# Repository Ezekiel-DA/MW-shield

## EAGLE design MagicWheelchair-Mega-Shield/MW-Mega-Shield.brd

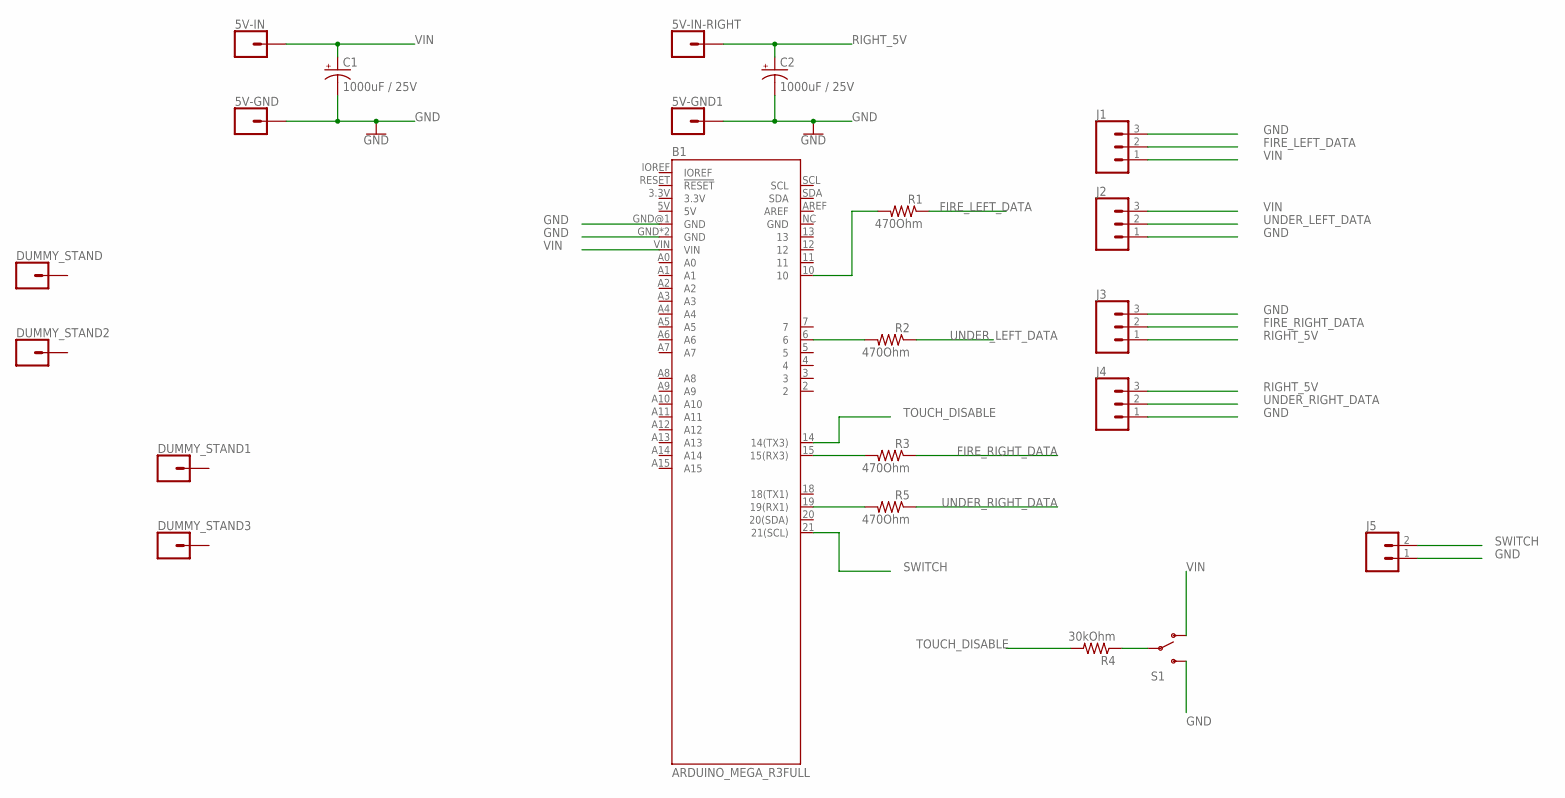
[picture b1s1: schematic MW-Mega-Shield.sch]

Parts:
5V-GND, 5V-GND1, 5V-IN, 5V-IN-RIGHT: CONN_01; 1X01
B1: ARDUINO_MEGA_R3FULL; ARDUINO_MEGA_NO_SILK
C1, C2: 1000uF / 25V; E5-10,5
DUMMY_STAND, DUMMY_STAND1, DUMMY_STAND2, DUMMY_STAND3: CONN_01; 1X01
J1, J2, J3, J4: CONN_03SCREW-NS; SCREWTERMINAL-3.5MM-3-NS
J5: CONN_02; 1X02
R1, R2, R3, R5: 470Ohm; R0603
R4: 30kOhm; R0603
S1: SWITCH-SPDTSMD; SWITCH_SPDT_SMD

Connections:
FIRE_LEFT_DATA: J1.2, R1.1
FIRE_RIGHT_DATA: J3.2, R3.1
GND: 5V-GND.1, 5V-GND1.1, B1.GND, B1.GND@1 (GND), B1.GND@4 (GND), C1.-, C2.-, J1.3, J2.1, J3.3, J4.1, J5.1, S1.3 (S)
unnamed: B1.10, R1.2
unnamed: B1.6, R2.2
unnamed: R4.1, S1.2
unnamed: B1.15 (15(RX3)), R3.2
unnamed: B1.19 (19(RX1)), R5.2
RIGHT_5V: 5V-IN-RIGHT.1, C2.+, J3.1, J4.3
SWITCH: B1.21 (21(SCL)), J5.2
TOUCH_DISABLE: B1.14 (14(TX3)), R4.2
UNDER_LEFT_DATA: J2.2, R2.1
UNDER_RIGHT_DATA: J4.2, R5.1
VIN: 5V-IN.1, B1.VIN, C1.+, J1.1, J2.3, S1.1 (O)

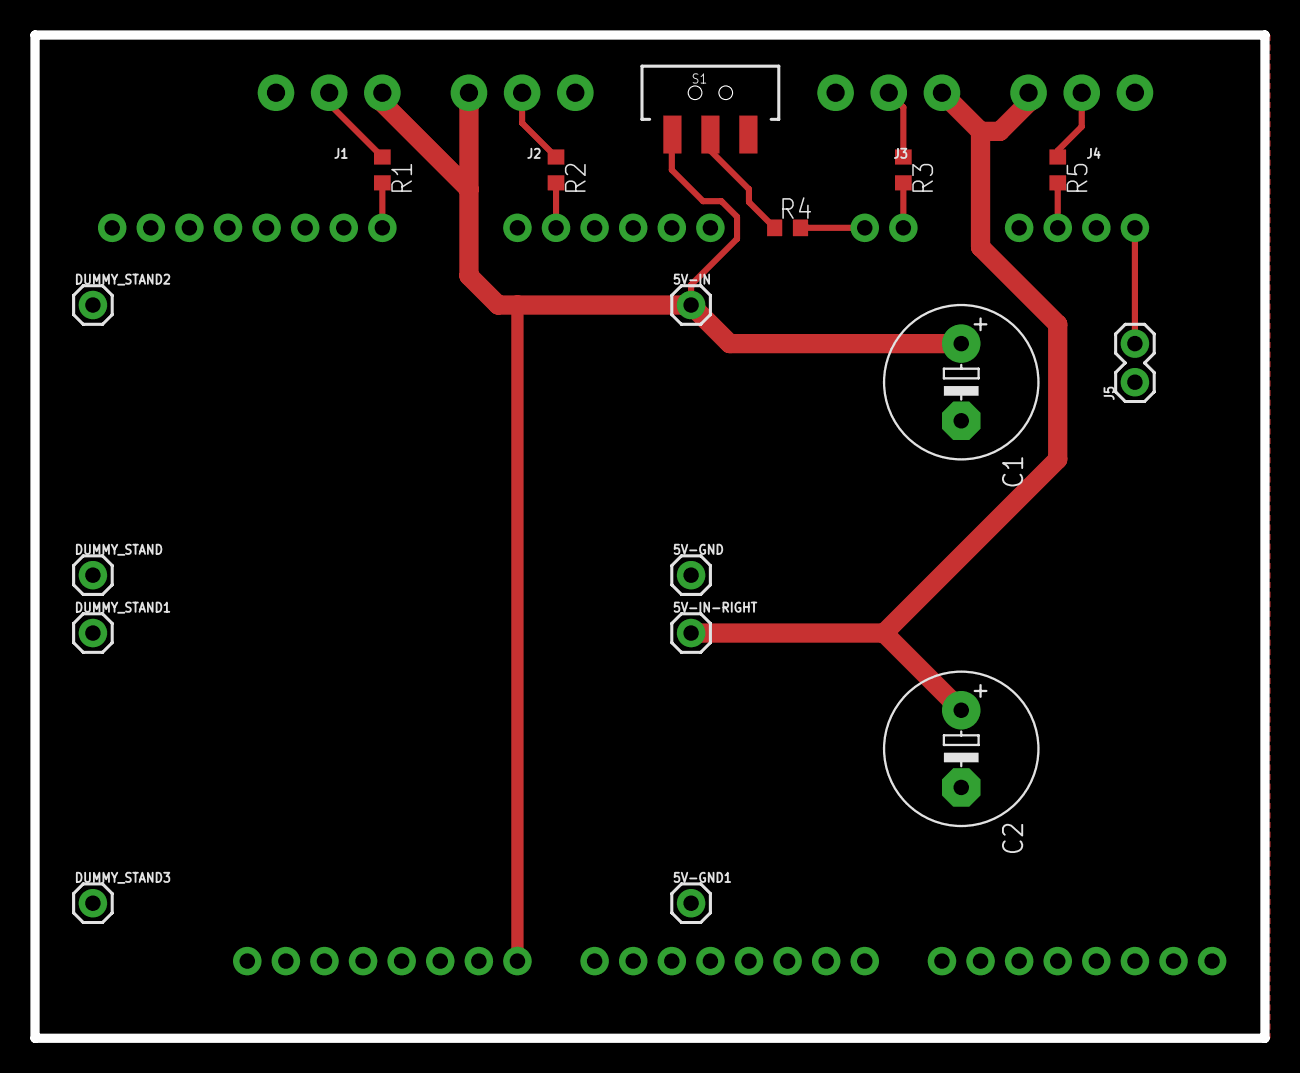
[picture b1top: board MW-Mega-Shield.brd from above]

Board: 2 copper layers, 80.9 x 66.0 mm, 22 parts (0 on the bottom side), 14 nets.

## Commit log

2018-06-05 Add first version of PCB
2018-06-05 Update PCB, add PNG version
2018-06-05 Add outline and trace PNGs
2018-06-06 Update PCB, better PNGs
2018-06-06 Fix pad separation, switch holes, etc
2018-06-06 Add master switch

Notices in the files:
parts and their libraries:
SparkFun-Connectors: Licensing: Creative Commons ShareAlike 4.0 International - https://creativecommons.org/licenses/by-sa/4.0
